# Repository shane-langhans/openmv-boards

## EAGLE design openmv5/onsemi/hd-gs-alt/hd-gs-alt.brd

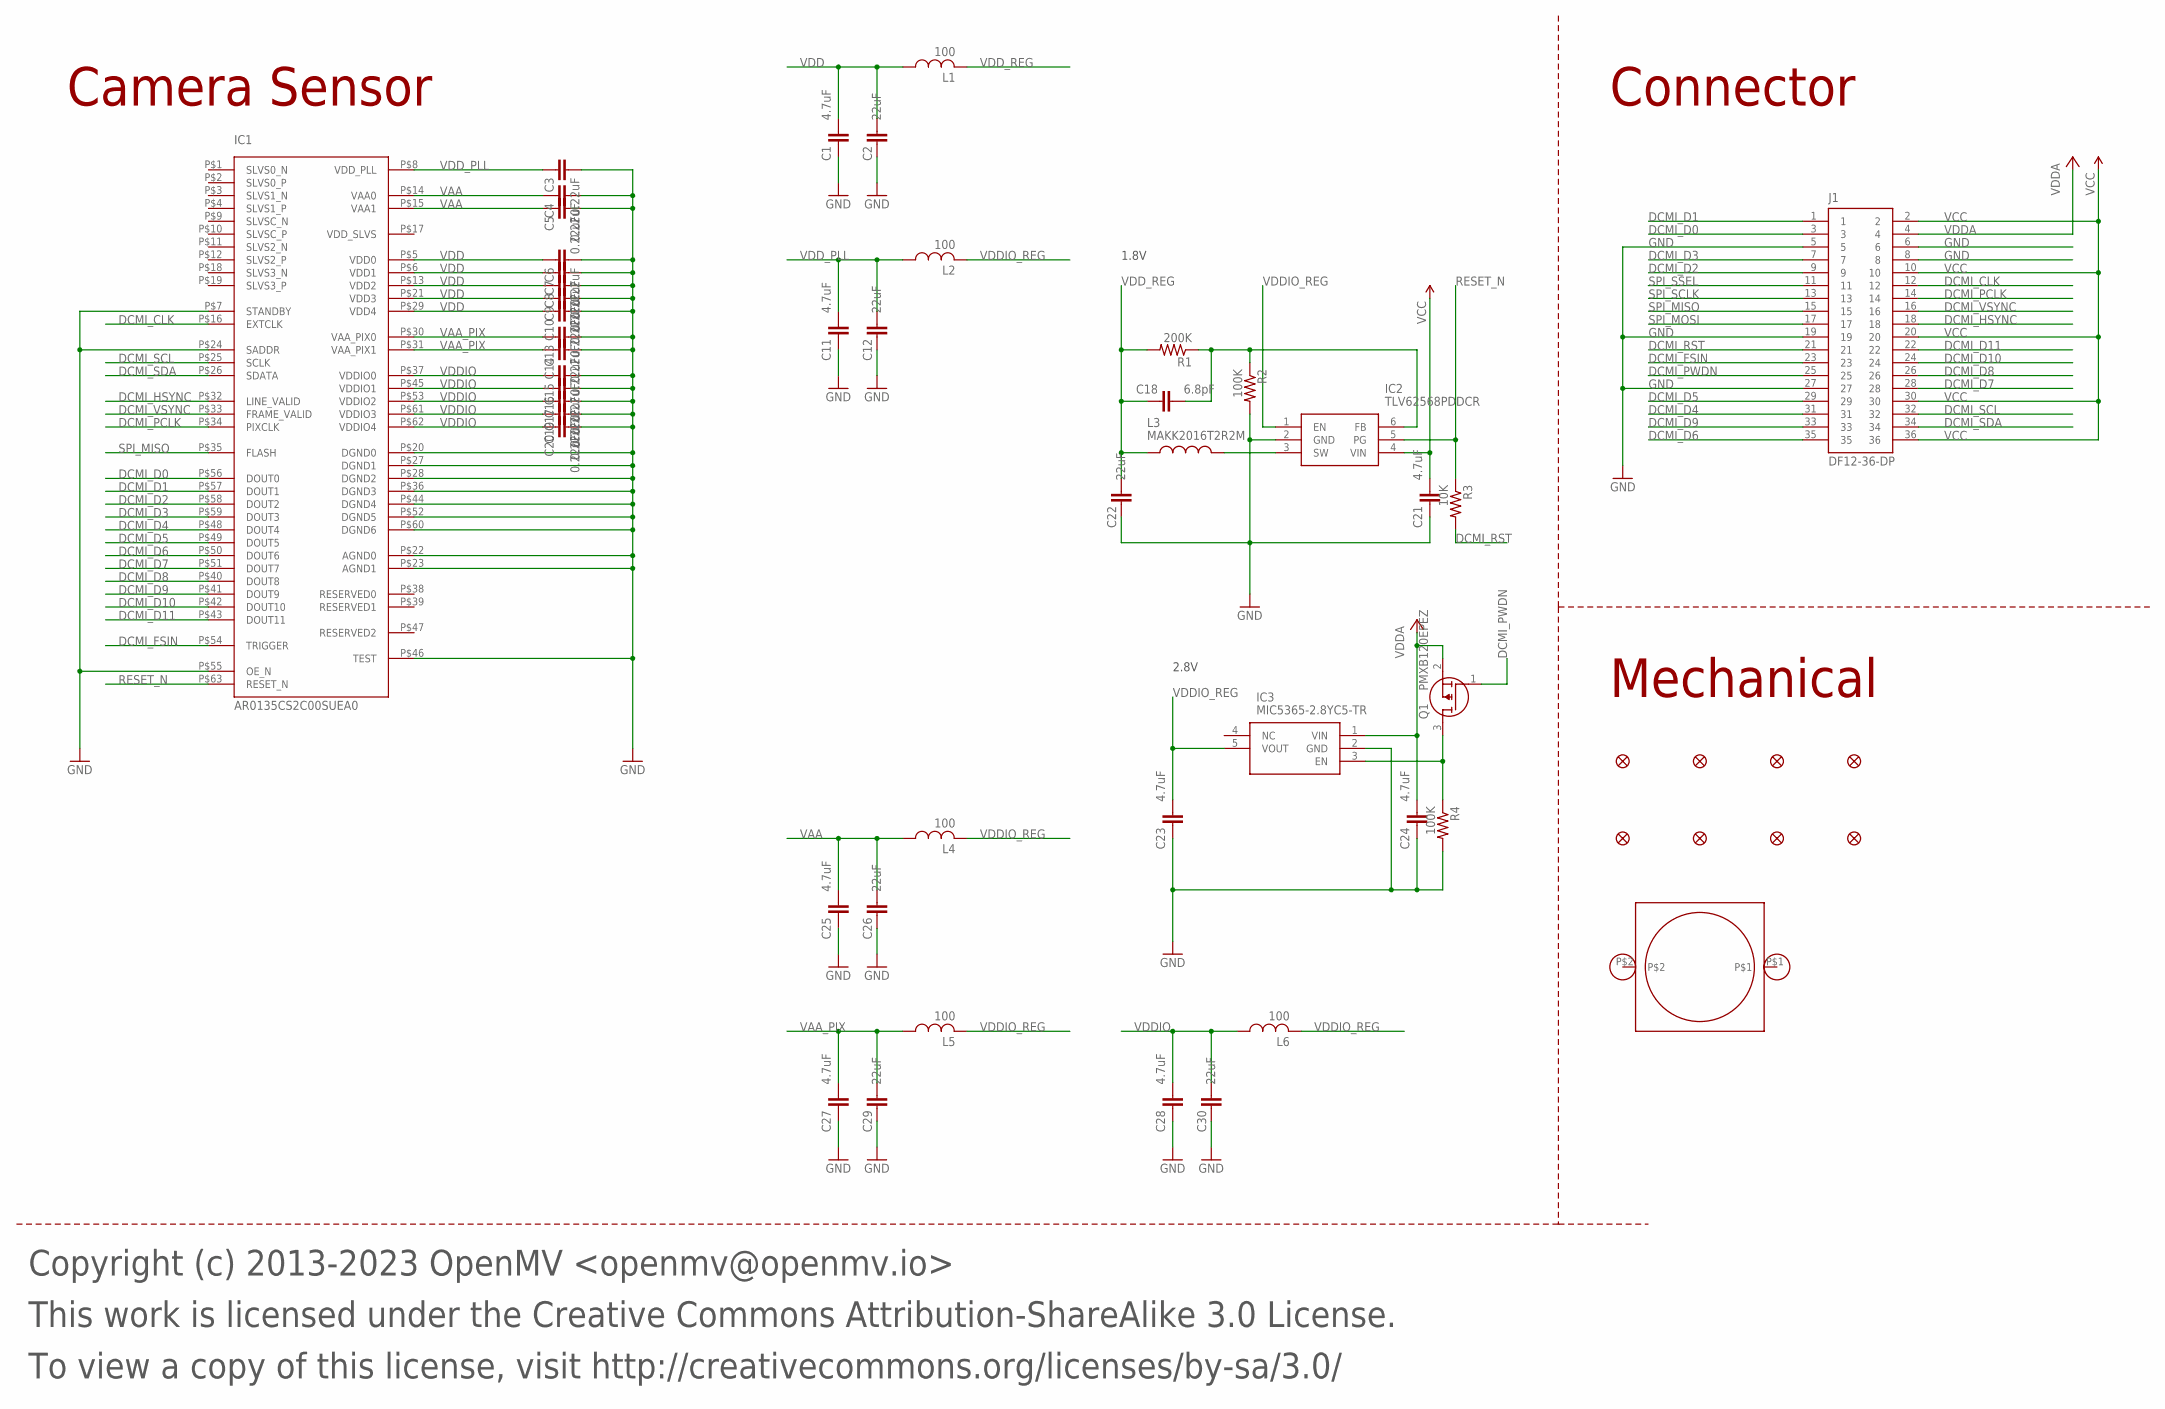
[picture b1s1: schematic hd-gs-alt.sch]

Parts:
C1, C11, C21, C23, C24, C25, C27, C28: 4.7uF; 0402; MPN JMK105BBJ475MV-F
C2, C12, C22, C26, C29, C30: 22uF; 0805; MPN CL21A226MQQNNNE
C3, C4, C5, C6, C7, C8, C9, C10, C13, C14, C15, C16, C17, C19, C20: 0.22uF; C0201; MPN GRM033R60J224ME15D
C18: 6.8pF; 0402; MPN GRM1555C1H6R8DA01D
FD1, FD2, FD3, FD4, FD5, FD6, FD7, FD8: FIDUCIAL1X2; FIDUCIAL-1X2
H1: LENSMOUNT20MM; LENSMOUNT-20MM
IC1: AR0135CS2C00SUEA0; MPN AR0135CS2C00SUEA0-DRBR
IC2: TLV62568PDDCR; SOT95P280X110-6N; MPN TLV62568PDDCR
IC3: MIC5365-2.8YC5-TR; SOT65P210X110-5N; MPN MIC5365-2.8YC5-TR
J1: DF12-36-DP; MPN DF12NB(3.0)-36DP-0.5V(51)
L1, L2, L4, L5, L6: 100; 0402; MPN MFBM1V1005-101-R
L3: MAKK2016T2R2M; INDC2016X100N; MPN MAKK2016T2R2M
Q1: PMXB120EPEZ; MPN PMXB120EPEZ
R1: 200K; R0402; MPN CRCW0402200KFKEDC
R2, R4: 100K; R0402; MPN AC0402FR-07100KL
R3: 10K; R0402; MPN AC0402FR-1310KL

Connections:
DCMI_CLK: IC1.P$16 (EXTCLK), J1.12
DCMI_D0: IC1.P$56 (DOUT0), J1.3
DCMI_D1: IC1.P$57 (DOUT1), J1.1
DCMI_D2: IC1.P$58 (DOUT2), J1.9
DCMI_D3: IC1.P$59 (DOUT3), J1.7
DCMI_D4: IC1.P$48 (DOUT4), J1.31
DCMI_D5: IC1.P$49 (DOUT5), J1.29
DCMI_D6: IC1.P$50 (DOUT6), J1.35
DCMI_D7: IC1.P$51 (DOUT7), J1.28
DCMI_D8: IC1.P$40 (DOUT8), J1.26
DCMI_D9: IC1.P$41 (DOUT9), J1.33
DCMI_D10: IC1.P$42 (DOUT10), J1.24
DCMI_D11: IC1.P$43 (DOUT11), J1.22
DCMI_FSIN: IC1.P$54 (TRIGGER), J1.23
DCMI_HSYNC: IC1.P$32 (LINE_VALID), J1.18
DCMI_PCLK: IC1.P$34 (PIXCLK), J1.14
DCMI_PWDN: J1.25, Q1.1 (G)
DCMI_PWDN_INT: IC3.3 (EN), Q1.3 (D), R4.1
DCMI_RST: J1.21, R3.2
DCMI_SCL: IC1.P$25 (SCLK), J1.32
DCMI_SDA: IC1.P$26 (SDATA), J1.34
DCMI_VSYNC: IC1.P$33 (FRAME_VALID), J1.16
FB: C18.2, IC2.6 (FB), R1.1, R2.1
GND: C1.1, C2.1, C3.2, C4.2, C5.2, C6.2, C7.2, C8.2, C9.2, C10.2, C11.1, C12.1, C13.2, C14.2, C15.2, C16.2, C17.2, C19.2, C20.2, C21.1, C22.1, C23.1, C24.1, C25.1, C26.1, C27.1, C28.1, C29.1, C30.1, IC1.P$7 (STANDBY), IC1.P$20 (DGND0), IC1.P$22 (AGND0), IC1.P$23 (AGND1), IC1.P$24 (SADDR), IC1.P$27 (DGND1), IC1.P$28 (DGND2), IC1.P$36 (DGND3), IC1.P$44 (DGND4), IC1.P$46 (TEST), IC1.P$52 (DGND5), IC1.P$55 (OE_N), IC1.P$60 (DGND6), IC2.2 (GND), IC3.2 (GND), J1.5, J1.6, J1.8, J1.19, J1.27, R2.2, R4.2
RESET_N: IC1.P$63 (RESET_N), IC2.5 (PG), R3.1
SPI_MISO: IC1.P$35 (FLASH), J1.15
SPI_MOSI: J1.17
SPI_SCLK: J1.13
SPI_SSEL: J1.11
SW: IC2.3 (SW), L3.2
VAA: C4.1, C5.1, C25.2, C26.2, IC1.P$14 (VAA0), IC1.P$15 (VAA1), L4.1
VAA_PIX: C13.1, C14.1, C27.2, C29.2, IC1.P$30 (VAA_PIX0), IC1.P$31 (VAA_PIX1), L5.1
VCC: C21.2, IC2.4 (VIN), J1.2, J1.10, J1.20, J1.30, J1.36
VDD: C1.2, C2.2, C6.1, C7.1, C8.1, C9.1, C10.1, IC1.P$5 (VDD0), IC1.P$6 (VDD1), IC1.P$13 (VDD2), IC1.P$21 (VDD3), IC1.P$29 (VDD4), L1.1
VDDA: C24.2, IC3.1 (VIN), J1.4, Q1.2 (S)
VDDIO: C15.1, C16.1, C17.1, C19.1, C20.1, C28.2, C30.2, IC1.P$37 (VDDIO0), IC1.P$45 (VDDIO1), IC1.P$53 (VDDIO2), IC1.P$61 (VDDIO3), IC1.P$62 (VDDIO4), L6.1
VDDIO_REG: C23.2, IC2.1 (EN), IC3.5 (VOUT), L2.2, L4.2, L5.2, L6.2
VDD_PLL: C3.1, C11.2, C12.2, IC1.P$8 (VDD_PLL), L2.1
VDD_REG: C18.1, C22.2, L1.2, L3.1, R1.2

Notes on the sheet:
Copyright (c) 2013-2023 OpenMV <openmv@openmv.io>
This work is licensed under the Creative Commons Attribution-ShareAlike 3.0 License.
To view a copy of this license, visit http://creativecommons.org/licenses/by-sa/3.0/
Camera Sensor
Mechanical
Connector
1.8V
2.8V

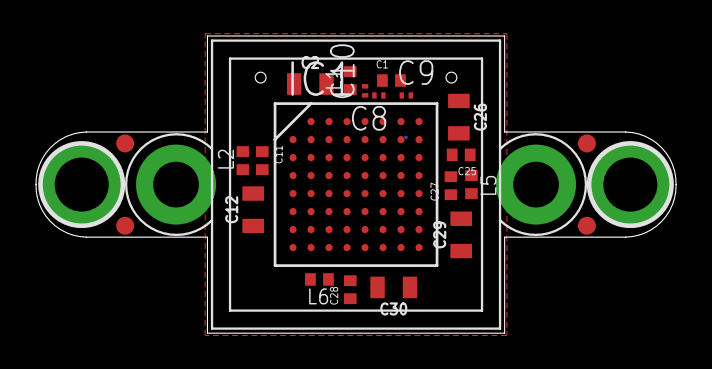
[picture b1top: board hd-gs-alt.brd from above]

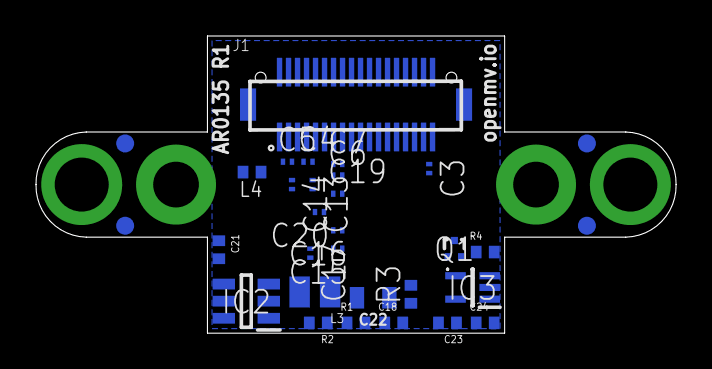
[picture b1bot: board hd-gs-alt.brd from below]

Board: 6 copper layers, 35.6 x 16.5 mm, 54 parts (31 on the bottom side), 36 nets.

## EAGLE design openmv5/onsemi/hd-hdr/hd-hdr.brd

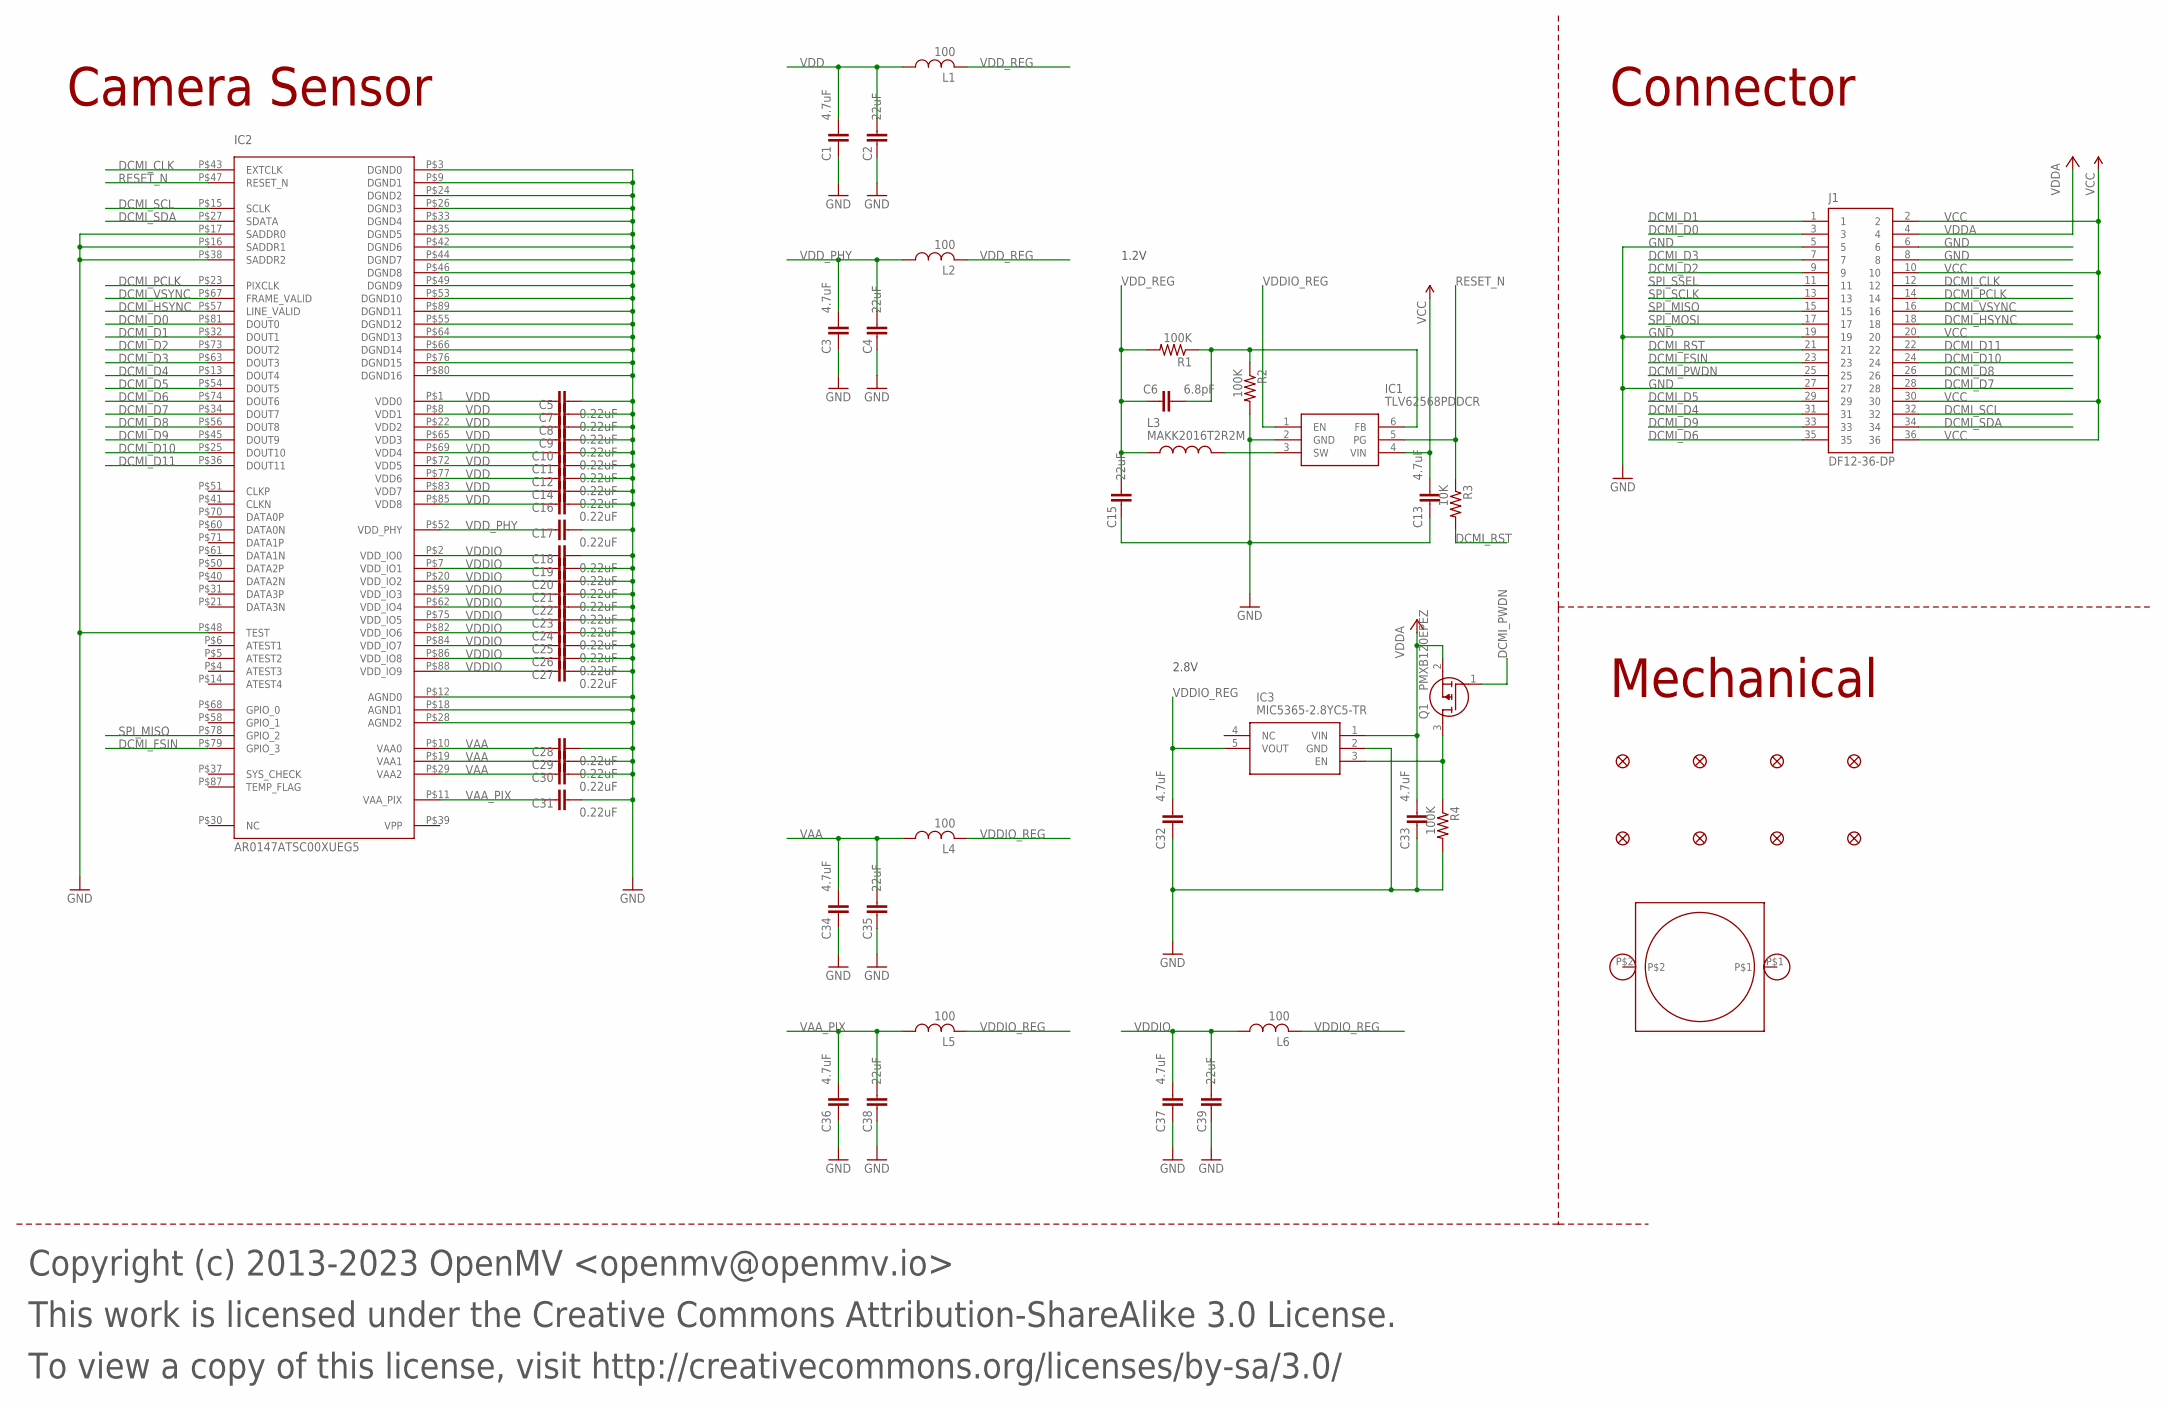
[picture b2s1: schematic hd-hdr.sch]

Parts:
C1, C3, C13, C32, C33, C34, C36, C37: 4.7uF; 0402; MPN JMK105BBJ475MV-F
C2, C4, C15, C35, C38, C39: 22uF; 0805; MPN CL21A226MQQNNNE
C5, C7, C8, C9, C10, C11, C12, C14, C16, C17, C18, C19, C20, C21, C22, C23, C24, C25, C26, C27, C28, C29, C30, C31: 0.22uF; C0201; MPN GRM033R60J224ME15D
C6: 6.8pF; 0402; MPN GRM1555C1H6R8DA01D
FD1, FD2, FD3, FD4, FD5, FD6, FD7, FD8: FIDUCIAL1X2; FIDUCIAL-1X2
H1: LENSMOUNT20MM; LENSMOUNT-20MM
IC1: TLV62568PDDCR; SOT95P280X110-6N; MPN TLV62568PDDCR
IC2: AR0147ATSC00XUEG5; MPN AR0147ATSC00XUEG5-DRBR
IC3: MIC5365-2.8YC5-TR; SOT65P210X110-5N; MPN MIC5365-2.8YC5-TR
J1: DF12-36-DP; MPN DF12NB(3.0)-36DP-0.5V(51)
L1, L2, L4, L5, L6: 100; 0402; MPN MFBM1V1005-101-R
L3: MAKK2016T2R2M; INDC2016X100N; MPN MAKK2016T2R2M
Q1: PMXB120EPEZ; MPN PMXB120EPEZ
R1, R2, R4: 100K; R0402; MPN AC0402FR-07100KL
R3: 10K; R0402; MPN AC0402FR-1310KL

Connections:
DCMI_CLK: IC2.P$43 (EXTCLK), J1.12
DCMI_D0: IC2.P$81 (DOUT0), J1.3
DCMI_D1: IC2.P$32 (DOUT1), J1.1
DCMI_D2: IC2.P$73 (DOUT2), J1.9
DCMI_D3: IC2.P$63 (DOUT3), J1.7
DCMI_D4: IC2.P$13 (DOUT4), J1.31
DCMI_D5: IC2.P$54 (DOUT5), J1.29
DCMI_D6: IC2.P$74 (DOUT6), J1.35
DCMI_D7: IC2.P$34 (DOUT7), J1.28
DCMI_D8: IC2.P$56 (DOUT8), J1.26
DCMI_D9: IC2.P$45 (DOUT9), J1.33
DCMI_D10: IC2.P$25 (DOUT10), J1.24
DCMI_D11: IC2.P$36 (DOUT11), J1.22
DCMI_FSIN: IC2.P$79 (GPIO_3), J1.23
DCMI_HSYNC: IC2.P$57 (LINE_VALID), J1.18
DCMI_PCLK: IC2.P$23 (PIXCLK), J1.14
DCMI_PWDN: J1.25, Q1.1 (G)
DCMI_PWDN_INT: IC3.3 (EN), Q1.3 (D), R4.1
DCMI_RST: J1.21, R3.2
DCMI_SCL: IC2.P$15 (SCLK), J1.32
DCMI_SDA: IC2.P$27 (SDATA), J1.34
DCMI_VSYNC: IC2.P$67 (FRAME_VALID), J1.16
FB: C6.2, IC1.6 (FB), R1.1, R2.1
GND: C1.1, C2.1, C3.1, C4.1, C5.2, C7.2, C8.2, C9.2, C10.2, C11.2, C12.2, C13.1, C14.2, C15.1, C16.2, C17.2, C18.2, C19.2, C20.2, C21.2, C22.2, C23.2, C24.2, C25.2, C26.2, C27.2, C28.2, C29.2, C30.2, C31.2, C32.1, C33.1, C34.1, C35.1, C36.1, C37.1, C38.1, C39.1, IC1.2 (GND), IC2.P$3 (DGND0), IC2.P$9 (DGND1), IC2.P$12 (AGND0), IC2.P$16 (SADDR1), IC2.P$17 (SADDR0), IC2.P$18 (AGND1), IC2.P$24 (DGND2), IC2.P$26 (DGND3), IC2.P$28 (AGND2), IC2.P$33 (DGND4), IC2.P$35 (DGND5), IC2.P$38 (SADDR2), IC2.P$42 (DGND6), IC2.P$44 (DGND7), IC2.P$46 (DGND8), IC2.P$48 (TEST), IC2.P$49 (DGND9), IC2.P$53 (DGND10), IC2.P$55 (DGND12), IC2.P$64 (DGND13), IC2.P$66 (DGND14), IC2.P$76 (DGND15), IC2.P$80 (DGND16), IC2.P$89 (DGND11), IC3.2 (GND), J1.5, J1.6, J1.8, J1.19, J1.27, R2.2, R4.2
RESET_N: IC1.5 (PG), IC2.P$47 (RESET_N), R3.1
SPI_MISO: IC2.P$78 (GPIO_2), J1.15
SPI_MOSI: J1.17
SPI_SCLK: J1.13
SPI_SSEL: J1.11
SW: IC1.3 (SW), L3.2
VAA: C28.1, C29.1, C30.1, C34.2, C35.2, IC2.P$10 (VAA0), IC2.P$19 (VAA1), IC2.P$29 (VAA2), L4.1
VAA_PIX: C31.1, C36.2, C38.2, IC2.P$11 (VAA_PIX), L5.1
VCC: C13.2, IC1.4 (VIN), J1.2, J1.10, J1.20, J1.30, J1.36
VDD: C1.2, C2.2, C5.1, C7.1, C8.1, C9.1, C10.1, C11.1, C12.1, C14.1, C16.1, IC2.P$1 (VDD0), IC2.P$8 (VDD1), IC2.P$22 (VDD2), IC2.P$65 (VDD3), IC2.P$69 (VDD4), IC2.P$72 (VDD5), IC2.P$77 (VDD6), IC2.P$83 (VDD7), IC2.P$85 (VDD8), L1.1
VDDA: C33.2, IC3.1 (VIN), J1.4, Q1.2 (S)
VDDIO: C18.1, C19.1, C20.1, C21.1, C22.1, C23.1, C24.1, C25.1, C26.1, C27.1, C37.2, C39.2, IC2.P$2 (VDD_IO0), IC2.P$7 (VDD_IO1), IC2.P$20 (VDD_IO2), IC2.P$59 (VDD_IO3), IC2.P$62 (VDD_IO4), IC2.P$75 (VDD_IO5), IC2.P$82 (VDD_IO6), IC2.P$84 (VDD_IO7), IC2.P$86 (VDD_IO8), IC2.P$88 (VDD_IO9), L6.1
VDDIO_REG: C32.2, IC1.1 (EN), IC3.5 (VOUT), L4.2, L5.2, L6.2
VDD_PHY: C3.2, C4.2, C17.1, IC2.P$52 (VDD_PHY), L2.1
VDD_REG: C6.1, C15.2, L1.2, L2.2, L3.1, R1.2

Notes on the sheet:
Copyright (c) 2013-2023 OpenMV <openmv@openmv.io>
This work is licensed under the Creative Commons Attribution-ShareAlike 3.0 License.
To view a copy of this license, visit http://creativecommons.org/licenses/by-sa/3.0/
Camera Sensor
Mechanical
Connector
1.2V
2.8V

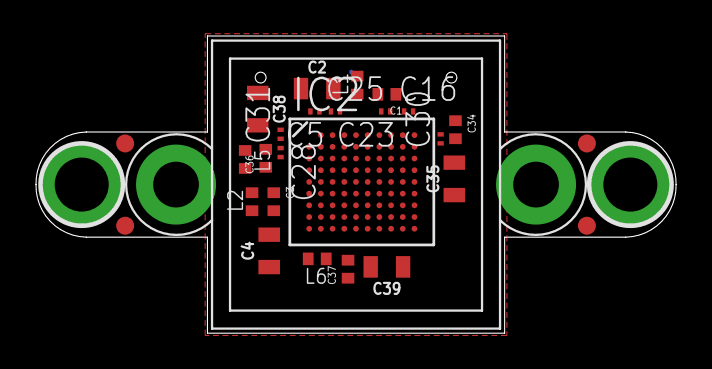
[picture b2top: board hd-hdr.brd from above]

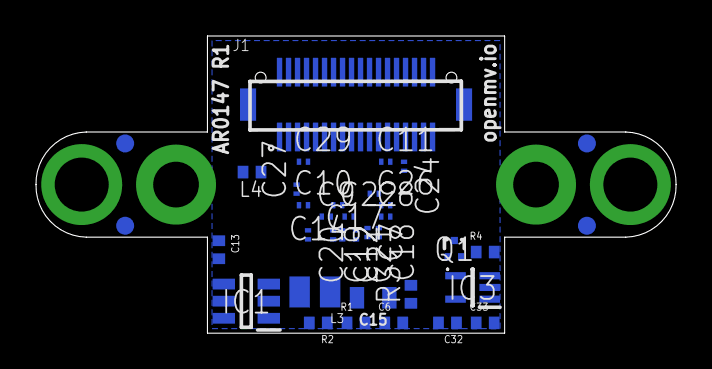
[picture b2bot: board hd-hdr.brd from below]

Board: 6 copper layers, 35.6 x 16.5 mm, 63 parts (36 on the bottom side), 36 nets.

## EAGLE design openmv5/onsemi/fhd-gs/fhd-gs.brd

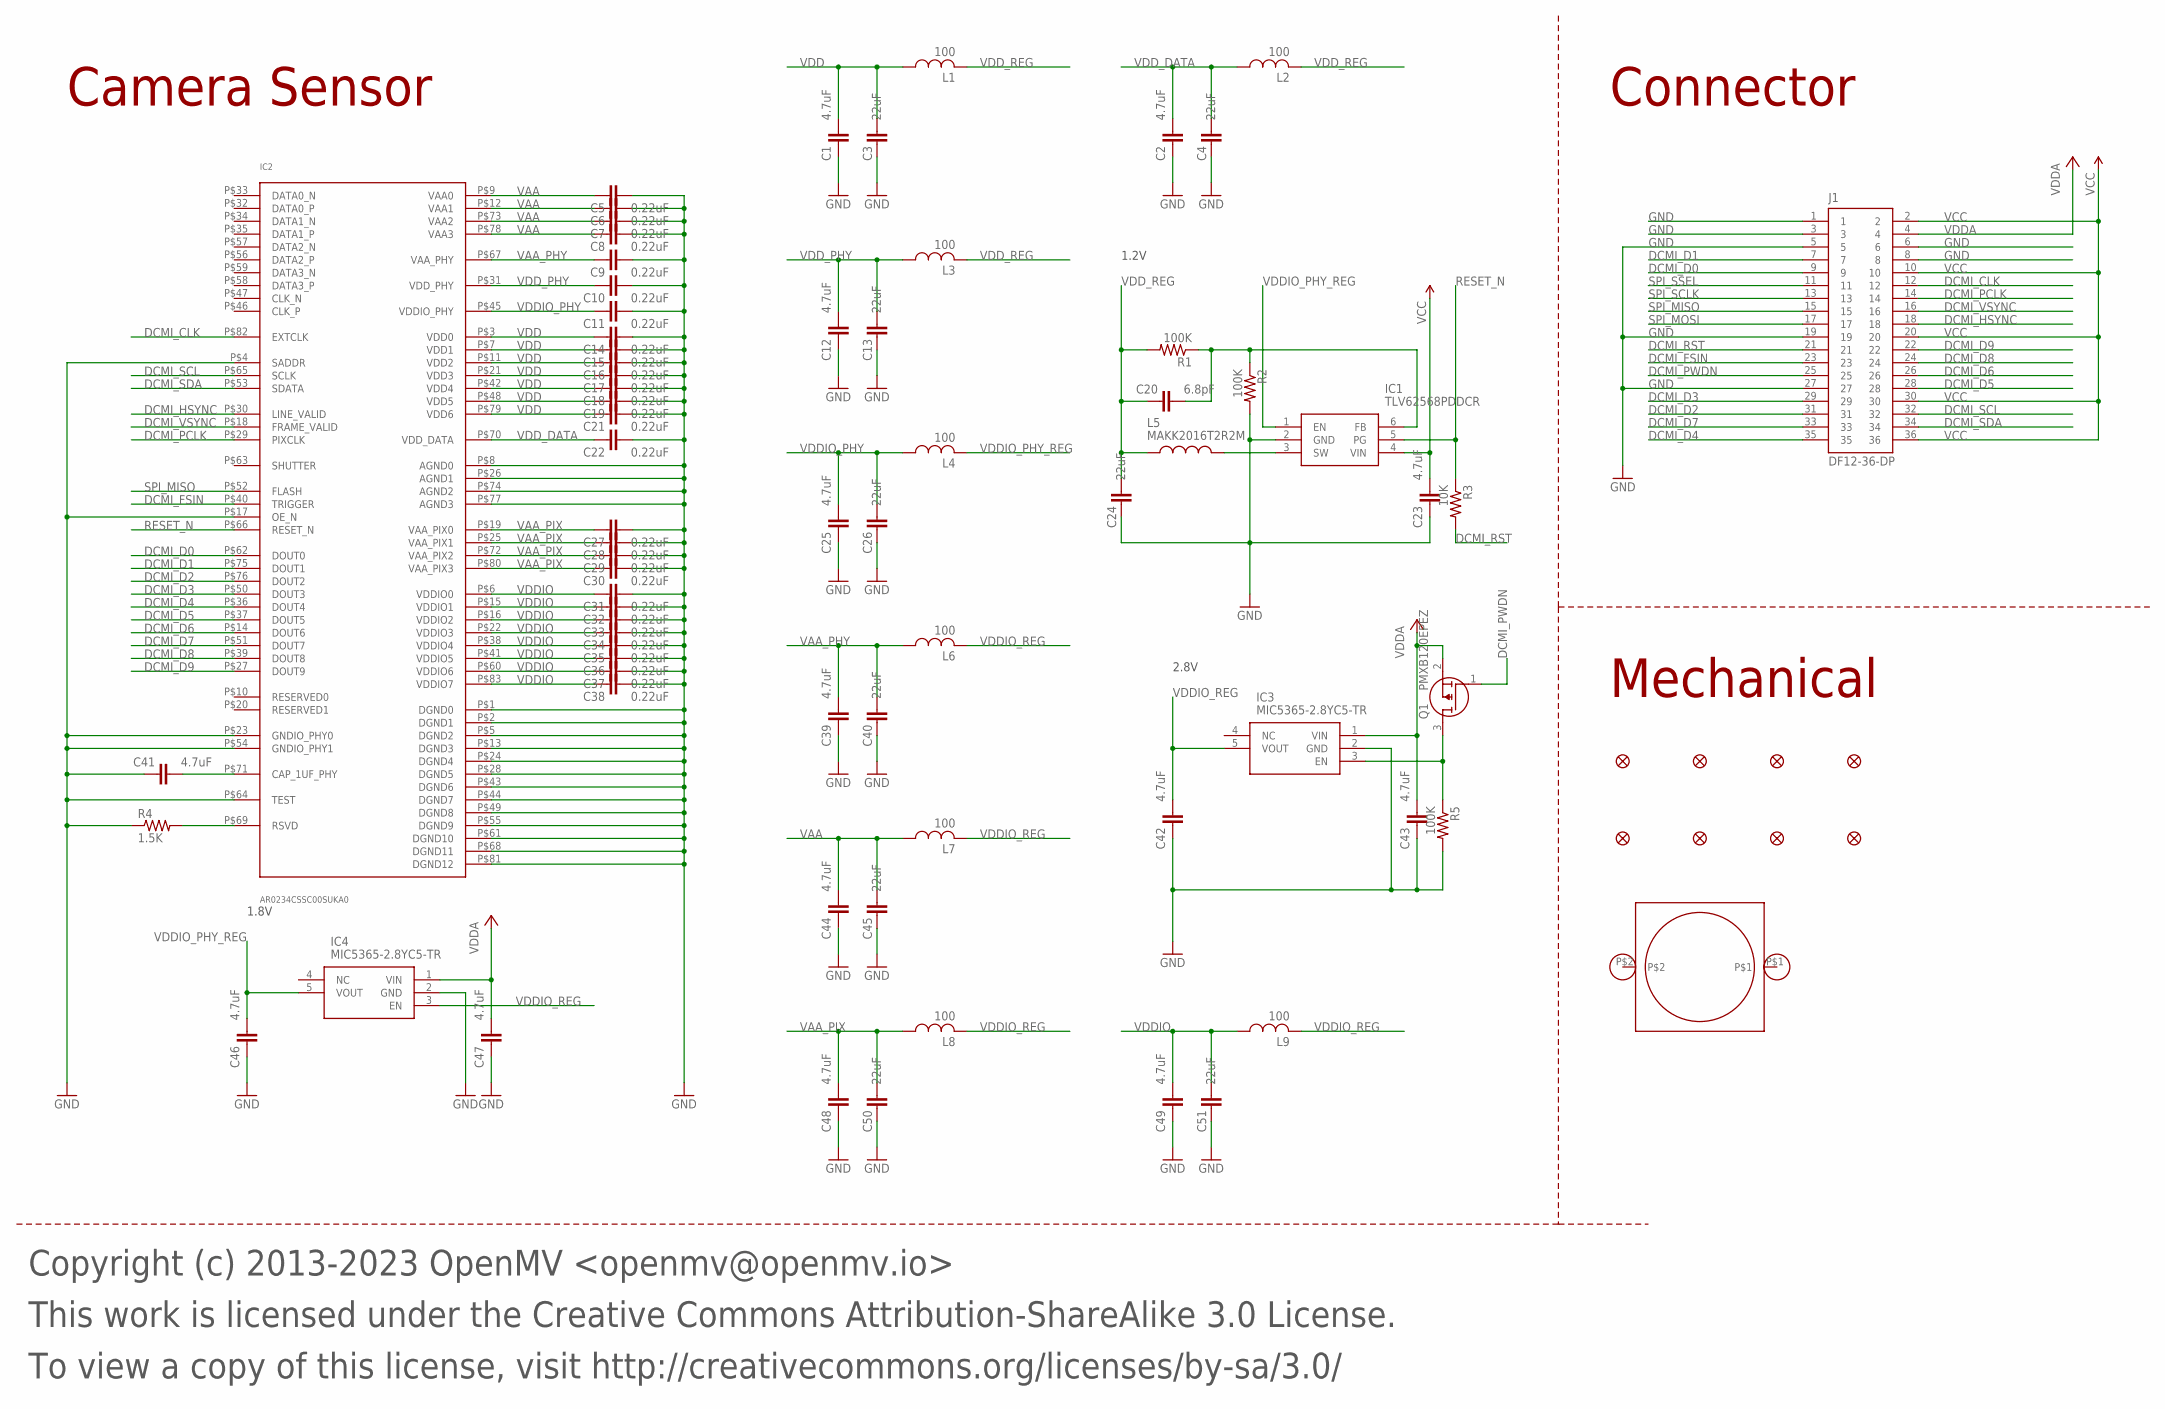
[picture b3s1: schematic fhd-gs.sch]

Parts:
C1, C2, C12, C23, C25, C39, C41, C42, C43, C44, C46, C47, C48, C49: 4.7uF; 0402; MPN JMK105BBJ475MV-F
C3, C4, C13, C24, C26, C40, C45, C50, C51: 22uF; 0805; MPN CL21A226MQQNNNE
C5, C6, C7, C8, C9, C10, C11, C14, C15, C16, C17, C18, C19, C21, C22, C27, C28, C29, C30, C31, C32, C33, C34, C35, C36, C37, C38: 0.22uF; C0201; MPN GRM033R60J224ME15D
C20: 6.8pF; 0402; MPN GRM1555C1H6R8DA01D
FD1, FD2, FD3, FD4, FD5, FD6, FD7, FD8: FIDUCIAL1X2; FIDUCIAL-1X2
H1: LENSMOUNT20MM; LENSMOUNT-20MM
IC1: TLV62568PDDCR; SOT95P280X110-6N; MPN TLV62568PDDCR
IC2: AR0234CSSC00SUKA0
IC3, IC4: MIC5365-2.8YC5-TR; SOT65P210X110-5N; MPN MIC5365-2.8YC5-TR
J1: DF12-36-DP; MPN DF12NB(3.0)-36DP-0.5V(51)
L1, L2, L3, L4, L6, L7, L8, L9: 100; 0402; MPN MFBM1V1005-101-R
L5: MAKK2016T2R2M; INDC2016X100N; MPN MAKK2016T2R2M
Q1: PMXB120EPEZ; MPN PMXB120EPEZ
R1, R2, R5: 100K; R0402; MPN AC0402FR-07100KL
R3: 10K; R0402; MPN AC0402FR-1310KL
R4: 1.5K; R0402; MPN RC0402FR-131K5L

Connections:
CAP: C41.2, IC2.P$71 (CAP_1UF_PHY)
DCMI_CLK: IC2.P$82 (EXTCLK), J1.12
DCMI_D0: IC2.P$62 (DOUT0), J1.9
DCMI_D1: IC2.P$75 (DOUT1), J1.7
DCMI_D2: IC2.P$76 (DOUT2), J1.31
DCMI_D3: IC2.P$50 (DOUT3), J1.29
DCMI_D4: IC2.P$36 (DOUT4), J1.35
DCMI_D5: IC2.P$37 (DOUT5), J1.28
DCMI_D6: IC2.P$14 (DOUT6), J1.26
DCMI_D7: IC2.P$51 (DOUT7), J1.33
DCMI_D8: IC2.P$39 (DOUT8), J1.24
DCMI_D9: IC2.P$27 (DOUT9), J1.22
DCMI_FSIN: IC2.P$40 (TRIGGER), J1.23
DCMI_HSYNC: IC2.P$30 (LINE_VALID), J1.18
DCMI_PCLK: IC2.P$29 (PIXCLK), J1.14
DCMI_PWDN: J1.25, Q1.1 (G)
DCMI_PWDN_INT: IC3.3 (EN), Q1.3 (D), R5.1
DCMI_RST: J1.21, R3.2
DCMI_SCL: IC2.P$65 (SCLK), J1.32
DCMI_SDA: IC2.P$53 (SDATA), J1.34
DCMI_VSYNC: IC2.P$18 (FRAME_VALID), J1.16
FB: C20.2, IC1.6 (FB), R1.1, R2.1
GND: C1.1, C2.1, C3.1, C4.1, C5.2, C6.2, C7.2, C8.2, C9.2, C10.2, C11.2, C12.1, C13.1, C14.2, C15.2, C16.2, C17.2, C18.2, C19.2, C21.2, C22.2, C23.1, C24.1, C25.1, C26.1, C27.2, C28.2, C29.2, C30.2, C31.2, C32.2, C33.2, C34.2, C35.2, C36.2, C37.2, C38.2, C39.1, C40.1, C41.1, C42.1, C43.1, C44.1, C45.1, C46.1, C47.1, C48.1, C49.1, C50.1, C51.1, IC1.2 (GND), IC2.P$1 (DGND0), IC2.P$2 (DGND1), IC2.P$4 (SADDR), IC2.P$5 (DGND2), IC2.P$8 (AGND0), IC2.P$13 (DGND3), IC2.P$17 (OE_N), IC2.P$23 (GNDIO_PHY0), IC2.P$24 (DGND4), IC2.P$26 (AGND1), IC2.P$28 (DGND5), IC2.P$43 (DGND6), IC2.P$44 (DGND7), IC2.P$49 (DGND8), IC2.P$54 (GNDIO_PHY1), IC2.P$55 (DGND9), IC2.P$61 (DGND10), IC2.P$64 (TEST), IC2.P$68 (DGND11), IC2.P$74 (AGND2), IC2.P$77 (AGND3), IC2.P$81 (DGND12), IC3.2 (GND), IC4.2 (GND), J1.1, J1.3, J1.5, J1.6, J1.8, J1.19, J1.27, R2.2, R4.1, R5.2
RESET_N: IC1.5 (PG), IC2.P$66 (RESET_N), R3.1
RSVD: IC2.P$69 (RSVD), R4.2
SPI_MISO: IC2.P$52 (FLASH), J1.15
SPI_MOSI: J1.17
SPI_SCLK: J1.13
SPI_SSEL: J1.11
SW: IC1.3 (SW), L5.2
VAA: C5.1, C6.1, C7.1, C8.1, C44.2, C45.2, IC2.P$9 (VAA0), IC2.P$12 (VAA1), IC2.P$73 (VAA2), IC2.P$78 (VAA3), L7.1
VAA_PHY: C9.1, C39.2, C40.2, IC2.P$67 (VAA_PHY), L6.1
VAA_PIX: C27.1, C28.1, C29.1, C30.1, C48.2, C50.2, IC2.P$19 (VAA_PIX0), IC2.P$25 (VAA_PIX1), IC2.P$72 (VAA_PIX2), IC2.P$80 (VAA_PIX3), L8.1
VCC: C23.2, IC1.4 (VIN), J1.2, J1.10, J1.20, J1.30, J1.36
VDD: C1.2, C3.2, C14.1, C15.1, C16.1, C17.1, C18.1, C19.1, C21.1, IC2.P$3 (VDD0), IC2.P$7 (VDD1), IC2.P$11 (VDD2), IC2.P$21 (VDD3), IC2.P$42 (VDD4), IC2.P$48 (VDD5), IC2.P$79 (VDD6), L1.1
VDDA: C43.2, C47.2, IC3.1 (VIN), IC4.1 (VIN), J1.4, Q1.2 (S)
VDDIO: C31.1, C32.1, C33.1, C34.1, C35.1, C36.1, C37.1, C38.1, C49.2, C51.2, IC2.P$6 (VDDIO0), IC2.P$15 (VDDIO1), IC2.P$16 (VDDIO2), IC2.P$22 (VDDIO3), IC2.P$38 (VDDIO4), IC2.P$41 (VDDIO5), IC2.P$60 (VDDIO6), IC2.P$83 (VDDIO7), L9.1
VDDIO_PHY: C11.1, C25.2, C26.2, IC2.P$45 (VDDIO_PHY), L4.1
VDDIO_PHY_REG: C46.2, IC1.1 (EN), IC4.5 (VOUT), L4.2
VDDIO_REG: C42.2, IC3.5 (VOUT), IC4.3 (EN), L6.2, L7.2, L8.2, L9.2
VDD_DATA: C2.2, C4.2, C22.1, IC2.P$70 (VDD_DATA), L2.1
VDD_PHY: C10.1, C12.2, C13.2, IC2.P$31 (VDD_PHY), L3.1
VDD_REG: C20.1, C24.2, L1.2, L2.2, L3.2, L5.1, R1.2

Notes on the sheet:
Copyright (c) 2013-2023 OpenMV <openmv@openmv.io>
This work is licensed under the Creative Commons Attribution-ShareAlike 3.0 License.
To view a copy of this license, visit http://creativecommons.org/licenses/by-sa/3.0/
Camera Sensor
Mechanical
Connector
1.2V
2.8V
1.8V

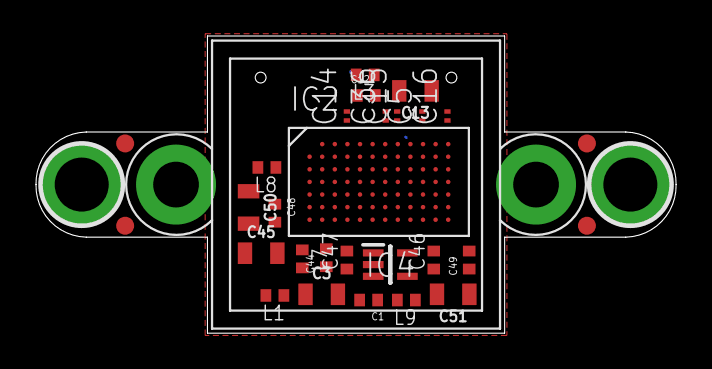
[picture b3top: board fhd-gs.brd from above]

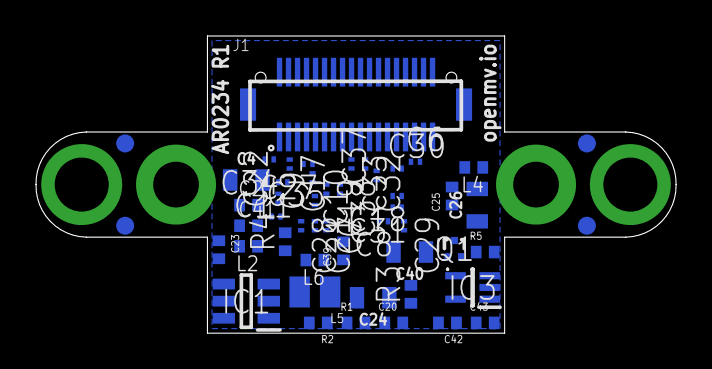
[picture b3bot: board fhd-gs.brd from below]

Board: 6 copper layers, 35.6 x 16.5 mm, 80 parts (51 on the bottom side), 40 nets.

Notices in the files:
parts and their libraries:
SparkFun-Aesthetics: Licensing: Creative Commons ShareAlike 4.0 International - https://creativecommons.org/licenses/by-sa/4.0
